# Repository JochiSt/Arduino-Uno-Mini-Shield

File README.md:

# Arduino-Uno-Mini-Shield
Shield template for [Arduino Uni Mini (limited edition)](https://docs.arduino.cc/hardware/uno-mini-le)

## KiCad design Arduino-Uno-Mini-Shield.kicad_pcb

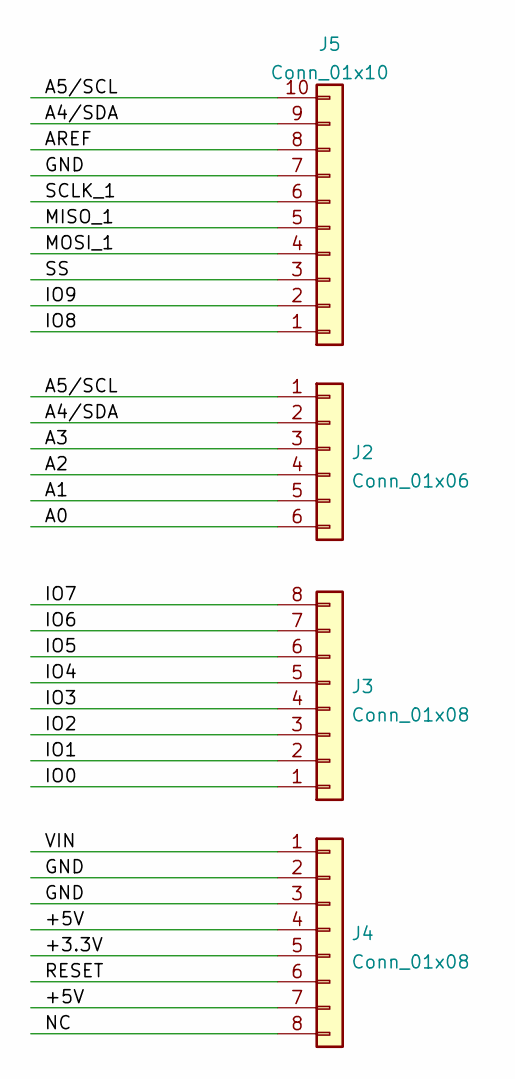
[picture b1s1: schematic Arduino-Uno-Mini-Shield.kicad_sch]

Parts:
J2: Conn_01x06; PinHeader_1x06_P1.27mm_Vertical
J3, J4: Conn_01x08; PinHeader_1x08_P1.27mm_Vertical
J5: Conn_01x10; PinHeader_1x10_P1.27mm_Vertical

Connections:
/+3.3V: J4.5
/+5V: J4.4, J4.7
/A0: J2.6
/A1: J2.5
/A2: J2.4
/A3: J2.3
/A4/SDA: J2.2, J5.9
/A5/SCL: J2.1, J5.10
/AREF: J5.8
/GND: J4.2, J4.3, J5.7
/IO0: J3.1
/IO1: J3.2
/IO2: J3.3
/IO3: J3.4
/IO4: J3.5
/IO5: J3.6
/IO6: J3.7
/IO7: J3.8
/IO8: J5.1
/IO9: J5.2
/MISO_1: J5.5
/MOSI_1: J5.4
/NC: J4.8
/RESET: J4.6
/SCLK_1: J5.6
/SS: J5.3
/VIN: J4.1

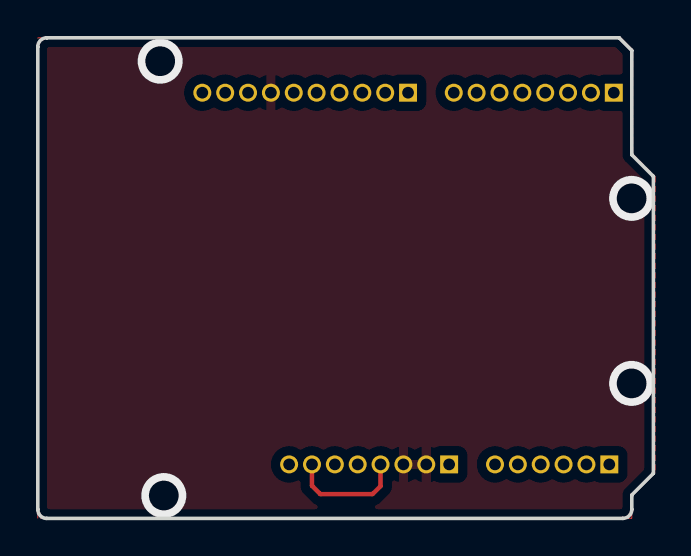
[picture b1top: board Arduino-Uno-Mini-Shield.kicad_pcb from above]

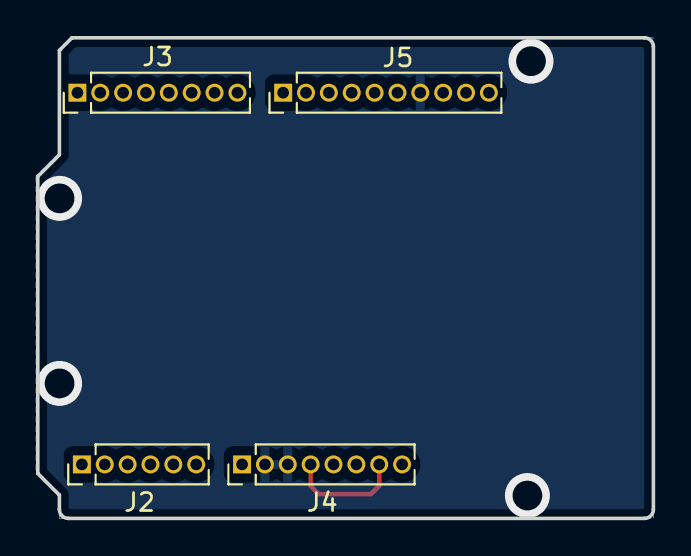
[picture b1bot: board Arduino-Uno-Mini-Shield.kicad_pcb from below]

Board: 2 copper layers, 34.2 x 26.7 mm, 4 parts (4 on the bottom side), 4 nets.

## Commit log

2022-01-24 added *.zip
2022-01-24 added 1st draft of layout
    added outline, pin header & their connection
    holes are just in Edges.Cut and not as holes. (TODO)
2022-01-24 ignore Altium documents
2022-01-24 fixed DRC
    There were some overlapping lines in Edge.Cuts
2022-01-25 final changes
    added VIAS as mounting holes
    added GND fill
    added +5V connection
